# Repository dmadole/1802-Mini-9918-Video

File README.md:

# 1802-Mini-9918-Video
This is the TMS9XXX video card for the [1802/Mini](https://github.com/dmadole/1802-Mini) system. It supports the following features:

* Supports TMS 9918/9118/9928/9128/9929/9129 video processors
* Composite video with 9X18 or component video with 9X2X
* Outputs video levels for 75-ohm or high-impedance inputs
* Separate negative sync output connector
* Supports group I/O port expansion
* Jumper-selected port address 1/5, 2/6, 3/7, 2/3, 4/5, or 6/7
* Jumper-selected interrupt polling bit on EF1-EF4

Gerber files for the PCBs and PDF schematics can be found in [Releases](https://github.com/dmadole/1802-Mini-9918-Video/releases).

BOMS and any applicable errata or other notes can be found in [notes](https://github.com/dmadole/1802-Mini-9918-Video/tree/main/notes).

For availability of kits and bare PCBs please see http://madole.net/1802/mini/kits

(Note that this photo is of a revision A board and address jumpers are slightly different than revision B boards. Do not use this photo for reference for jumpers.)

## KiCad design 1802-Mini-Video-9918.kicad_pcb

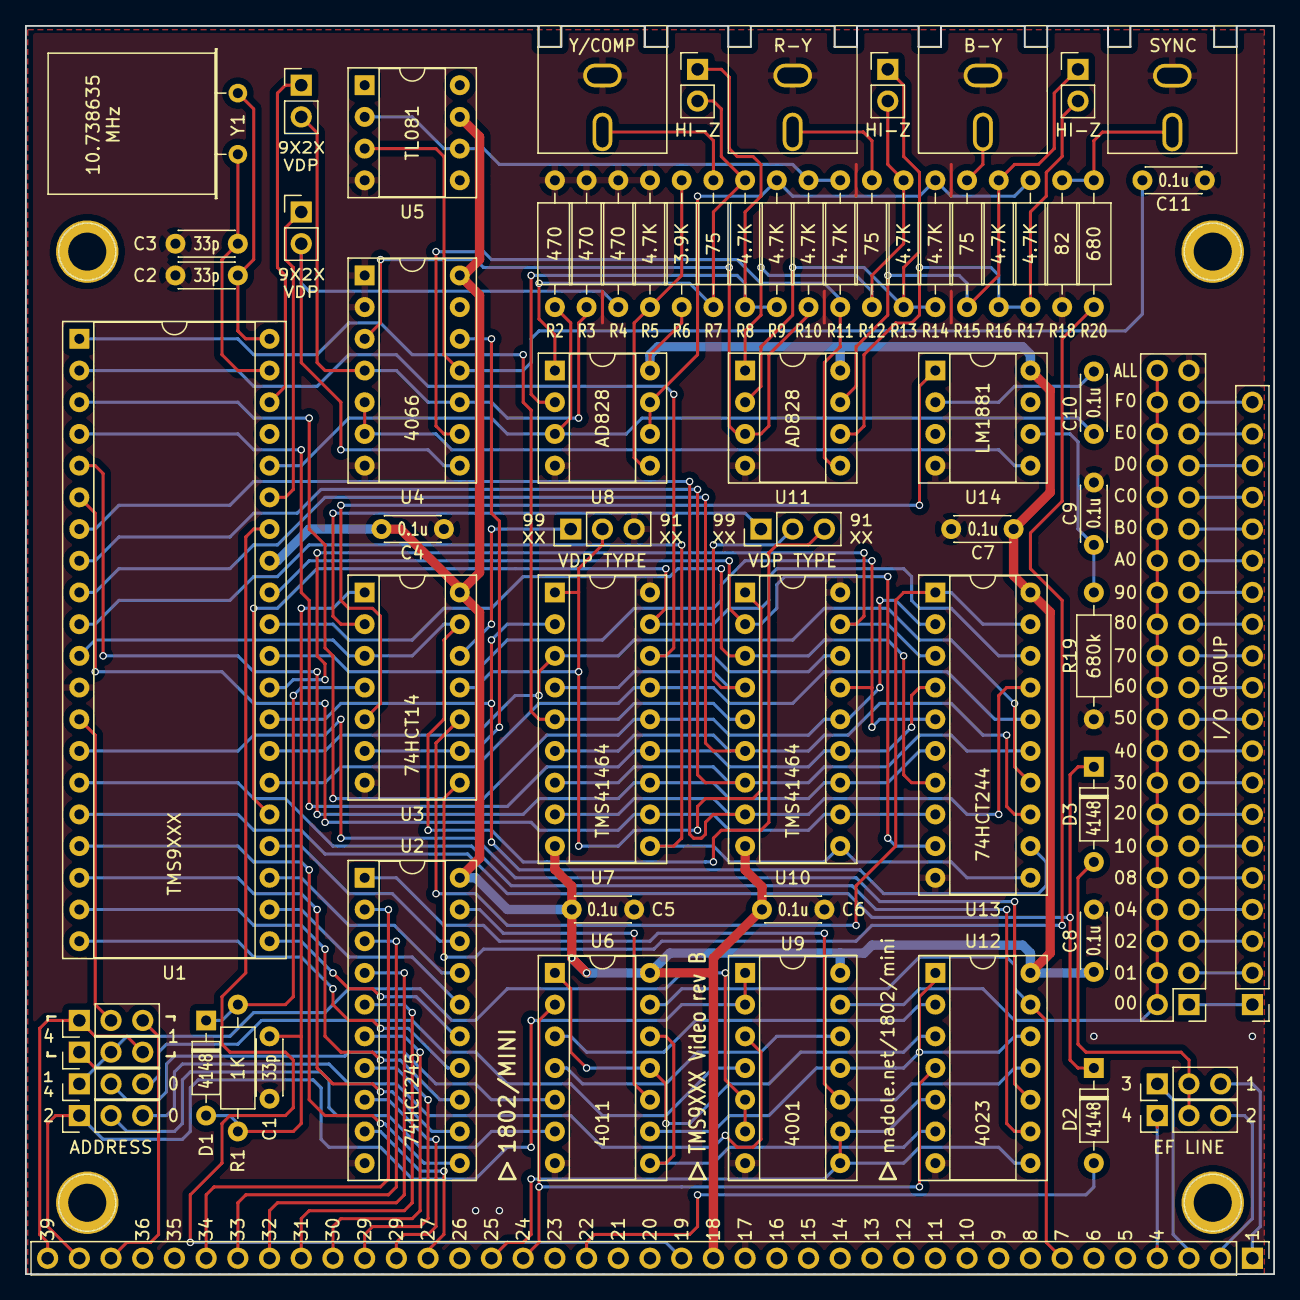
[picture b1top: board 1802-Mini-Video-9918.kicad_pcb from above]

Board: 2 copper layers, 100.0 x 100.0 mm, 73 parts (0 on the bottom side), 123 nets.

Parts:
C1, C2, C3: 33p; C_Disc_D4.3mm_W1.9mm_P5.00mm
C4, C5, C6, C7, C8, C9, C10, C11: 0.1u; C_Disc_D4.3mm_W1.9mm_P5.00mm
D1, D2, D3: 4148; D_DO-35_SOD27_P7.62mm_Horizontal
J1: Expansion; PinHeader_1x39_P2.54mm_Vertical
J2: GRP_EXP; PinHeader_1x20_P2.54mm_Vertical
J3: GRP_SEL; PinHeader_2x21_P2.54mm_Vertical
J5: Y/COMP; CUI RCJ-04X
J7: R-Y; CUI RCJ-04X
J9: B-Y; CUI RCJ-04X
J11: SYNC; CUI RCJ-04X
JP1: ADSEL2; PinHeader_1x03_P2.54mm_Vertical
JP2: ADSEL1; PinHeader_1x03_P2.54mm_Vertical
JP3: ADDR1/4; PinHeader_1x03_P2.54mm_Vertical
JP4, JP8, JP9: ADDR2; PinHeader_1x03_P2.54mm_Vertical
JP5, JP6, JP7: HI-Z; PinHeader_1x02_P2.54mm_Vertical
JP10: GSEL; PinHeader_1x03_P2.54mm_Vertical
JP11: WSEL; PinHeader_1x03_P2.54mm_Vertical
JP12, JP13: 9X2X; PinHeader_1x02_P2.54mm_Vertical
P6, P7, P8, P9: CONN_01X01; 1pin
R1: 1K; R_Axial_DIN0207_L6.3mm_D2.5mm_P10.16mm_Horizontal
R2, R3, R4: 470; R_Axial_DIN0207_L6.3mm_D2.5mm_P10.16mm_Horizontal
R5, R8, R9, R10, R11, R13, R14, R16, R17: 4.7K; R_Axial_DIN0207_L6.3mm_D2.5mm_P10.16mm_Horizontal
R6: 3.9K; R_Axial_DIN0207_L6.3mm_D2.5mm_P10.16mm_Horizontal
R7, R12, R15: 75; R_Axial_DIN0207_L6.3mm_D2.5mm_P10.16mm_Horizontal
R18: 82; R_Axial_DIN0207_L6.3mm_D2.5mm_P10.16mm_Horizontal
R19: 680k; R_Axial_DIN0207_L6.3mm_D2.5mm_P10.16mm_Horizontal
R20: 680; R_Axial_DIN0207_L6.3mm_D2.5mm_P10.16mm_Horizontal
U1: TMS9XXX; DIP-40_W15.24mm_Socket
U2: 74HCT245; DIP-20_W7.62mm_Socket
U3: 74HCT14; DIP-14_W7.62mm_Socket
U4: 4066; DIP-14_W7.62mm_Socket
U5: TL081; DIP-8_W7.62mm_Socket
U6: 4011; DIP-14_W7.62mm_Socket
U7, U10: TMS41464; DIP-18_W7.62mm_Socket
U8, U11: AD828; DIP-8_W7.62mm_Socket
U9: 4001; DIP-14_W7.62mm_Socket
U12: 4023; DIP-14_W7.62mm_Socket
U13: 74HCT244; DIP-20_W7.62mm_Socket
U14: LM1881; DIP-8_W7.62mm_Socket
Y1: Crystal; Crystal_HC49-U_Horizontal

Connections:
/AD0: U1.10, U7.10, U10.10, U13.11
/AD1: U1.9, U7.6, U10.6, U13.13
/AD2: U1.8, U7.7, U10.7, U13.15
/AD3: U1.7, U7.8, U10.8, U13.17
/AD4: U1.6, U7.11, U10.11, U13.8
/AD5: U1.5, U7.12, U10.12, U13.6
/AD6: U1.4, U7.13, U10.13, U13.4
/AD7: U1.3, U7.14, U10.14, U13.2
/BUS0: J1.27, U2.9
/BUS1: J1.28, U2.8
/BUS2: J1.29, U2.7
/BUS3: J1.30, U2.6
/BUS4: J1.31, U2.5
/BUS5: J1.32, U2.4
/BUS6: J1.33, U2.3
/BUS7: J1.34, U2.2
/RD0: U1.32, U10.2, U13.9
/RD1: U1.31, U10.3, U13.7
/RD2: U1.30, U10.15, U13.5
/RD3: U1.29, U10.17, U13.3
/RD4: U1.28, U7.2, U13.12
/RD5: U1.27, U7.3, U13.14
/RD6: U1.26, U7.15, U13.16
/RD7: U1.25, U7.17, U13.18
GND: C1.2, C2.2, C3.2, C4.1, C5.1, C6.1, C7.1, C8.1, C9.2, C11.1, J1.17, J3.41, J5.2, J7.2, J9.2, J11.2, JP10.3, R2.2, R3.2, R4.2, R5.2, R18.2, R19.1, U1.12, U2.10, U3.7, U4.1, U4.2, U4.7, U4.13, U5.4, U6.7, U7.18, U8.4, U9.7, U10.18, U11.4, U12.7, U13.10, U14.4
N0: J1.39, JP1.1, JP2.3
N1: J1.38, JP4.1, U9.1, U9.2
N2: J1.37, JP1.3, JP2.1
unnamed: C1.1, D1.2, R1.1, U3.1
unnamed: C2.1, U1.40, Y1.1
unnamed: C3.1, U1.39, Y1.2
unnamed: C9.1, R19.2, U14.6
unnamed: C10.1, R2.1, U1.36, U8.3
unnamed: C10.2, U14.2
unnamed: C11.2, U4.11, U5.3
unnamed: D1.1, R1.2, U3.4
unnamed: D2.1, D3.1, U1.16
unnamed: D3.2, JP8.2, JP9.2
unnamed: J2.1, J3.1
unnamed: J2.2, J3.3
unnamed: J2.3, J3.5
unnamed: J2.4, J3.7
unnamed: J2.5, J3.9
unnamed: J2.6, J3.11
unnamed: J2.7, J3.13
unnamed: J2.8, J3.15
unnamed: J2.9, J3.17
unnamed: J2.10, J3.19
unnamed: J2.11, J3.21
unnamed: J2.12, J3.23
unnamed: J2.13, J3.25
unnamed: J2.14, J3.27
unnamed: J2.15, J3.29
unnamed: J2.16, J3.31
unnamed: J2.17, J3.33
unnamed: J2.18, J3.35
unnamed: J2.19, J3.37
unnamed: J2.20, J3.39
unnamed: J5.1, R7.2
unnamed: J7.1, R12.2
unnamed: J9.1, R15.2
unnamed: J11.1, R18.1, R20.2
unnamed: JP1.2, U1.13
unnamed: JP2.2, JP3.1, U9.5, U9.6
unnamed: JP3.2, U6.5
unnamed: JP3.3, U9.4
unnamed: JP4.2, U6.6
unnamed: JP4.3, U9.3
unnamed: JP5.1, R8.1, R9.1, U8.2
unnamed: JP5.2, R7.1, R8.2, U8.1
unnamed: JP6.1, R13.1, R14.1, U11.2
unnamed: JP6.2, R12.1, R13.2, U11.1
unnamed: JP7.1, R15.1, R16.2, U11.7
unnamed: JP7.2, R16.1, R17.1, U11.6
unnamed: JP10.1, U3.12
unnamed: JP10.2, U3.11, U7.1, U10.1
unnamed: JP11.1, U3.2
unnamed: JP11.2, U7.4, U10.4
unnamed: JP11.3, U1.11, U3.3, U3.13
unnamed: JP12.1, U1.35
unnamed: JP12.2, R4.1, U4.8
unnamed: JP13.1, U1.38
unnamed: JP13.2, R3.1, U4.4, U4.10
unnamed: R5.1, R6.2, U8.5
unnamed: R10.1, U4.3, U11.3
unnamed: R10.2, R11.2, U5.2, U5.6
unnamed: R11.1, U4.9, U11.5
unnamed: R9.2, R14.2, R17.2, U8.6, U8.7
unnamed: R20.1, U3.8
unnamed: U1.1, U7.5, U10.5
unnamed: U1.2, U7.16, U10.16
unnamed: U1.14, U12.10
unnamed: U1.15, U12.9
unnamed: U1.17, U2.11
unnamed: U1.18, U2.12
unnamed: U1.19, U2.13
unnamed: U1.20, U2.14
unnamed: U1.21, U2.15
unnamed: U1.22, U2.16
unnamed: U1.23, U2.17
unnamed: U1.24, U2.18
unnamed: U2.19, U6.10
unnamed: U3.6, U3.9, U4.12
unnamed: U6.4, U9.12
unnamed: U6.9, U9.11, U12.1, U12.12
unnamed: U6.3, U12.2
unnamed: U6.1, U6.11, U12.3
unnamed: U6.8, U6.12, U12.6
unnamed: U2.1, U9.10, U12.11
unnamed: U3.10, U13.1, U13.19
unnamed: U3.5, U14.1
unnamed: U4.5, U4.6, U14.5
TPB: J1.7, U6.13, U12.13
VCC: C4.2, C5.2, C6.2, C7.2, C8.2, J1.18, R6.1, U1.33, U2.20, U3.14, U4.14, U5.7, U6.14, U7.9, U8.8, U9.14, U10.9, U11.8, U12.14, U13.20, U14.8
~CLEAR: J1.19, U1.34
~EF1: J1.1, JP8.3
~EF2: J1.2, JP9.3
~EF3: J1.3, JP8.1
~EF4: J1.4, JP9.1
~GROUP: J3.2, J3.4, J3.6, J3.8, J3.10, J3.12, J3.14, J3.16, J3.18, J3.20, J3.22, J3.24, J3.26, J3.28, J3.30, J3.32, J3.34, J3.36, J3.38, J3.40, J3.42, U9.13
~INT: D2.2, J1.22
~MRD: J1.25, U9.8, U9.9, U12.5, U12.8
~MWR: J1.24, U6.2, U12.4

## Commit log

2022-05-19 Remove incorrect comments on interrupts
